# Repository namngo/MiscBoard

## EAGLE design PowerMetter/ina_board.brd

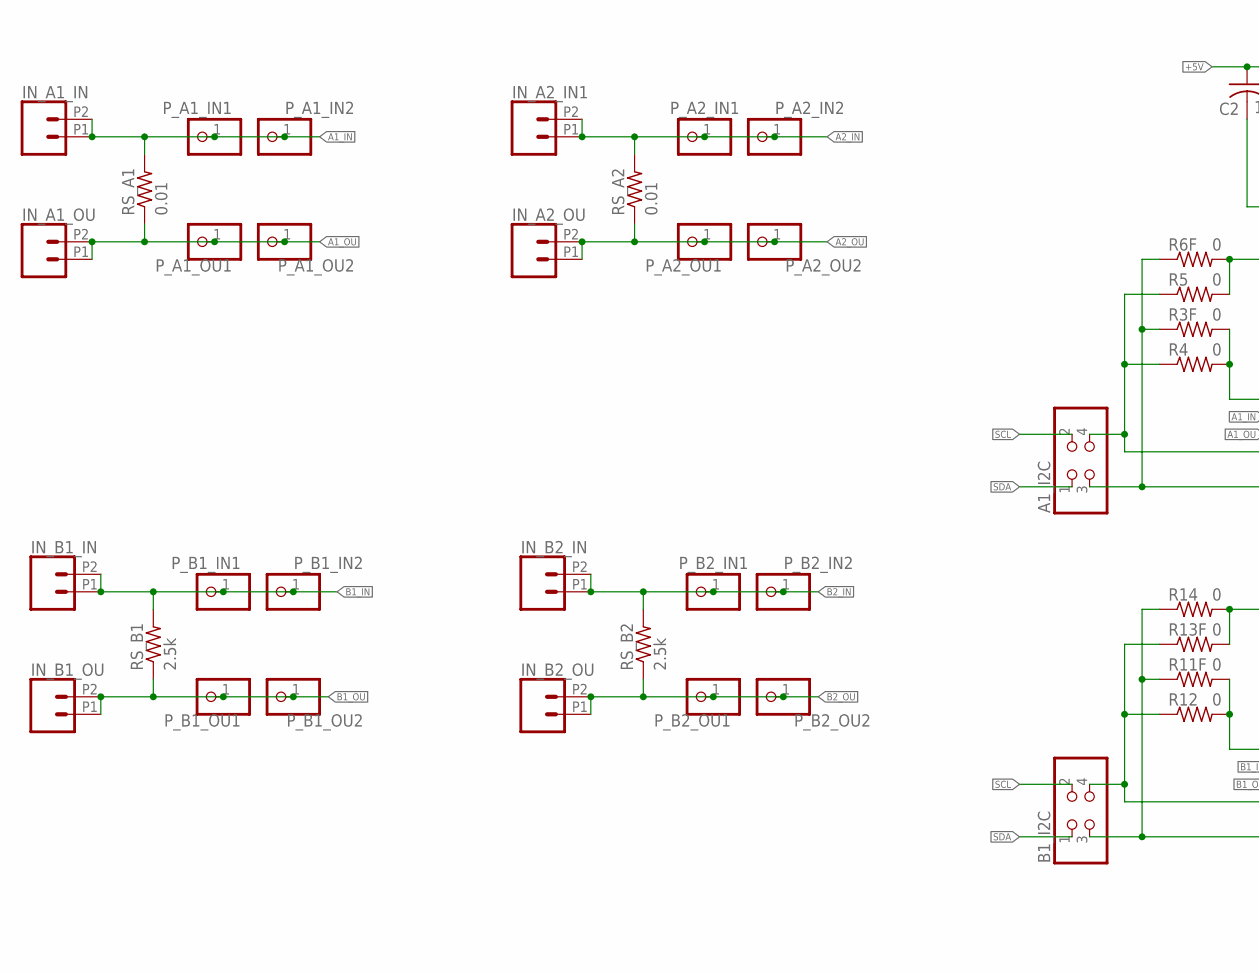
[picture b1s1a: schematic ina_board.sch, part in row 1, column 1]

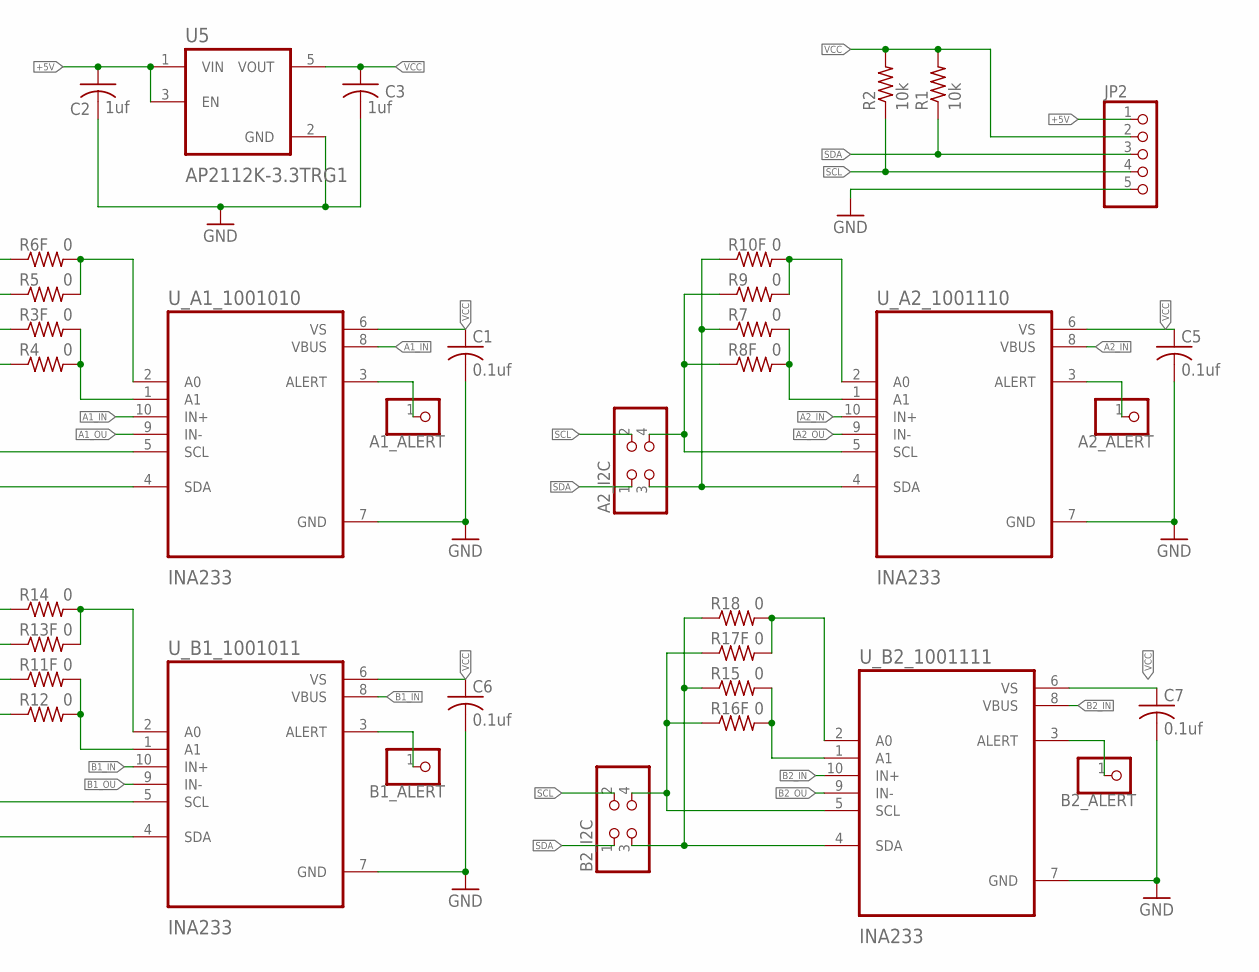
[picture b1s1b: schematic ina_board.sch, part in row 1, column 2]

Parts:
A1_ALERT, A2_ALERT: PINHD-1X1; 1X01
A1_I2C, A2_I2C: PINHD-2X2; 2X02
B1_ALERT, B2_ALERT: PINHD-1X1; 1X01
B1_I2C, B2_I2C: PINHD-2X2; 2X02
C1, C5, C6, C7: 0.1uf; C0805
C2, C3: 1uf; C1210
IN_A1_IN, IN_A1_OU, IN_A2_IN1, IN_A2_OU: CONN_022.54MM_SCREWTERM; 1X02_2.54_SCREWTERM
IN_B1_IN, IN_B1_OU, IN_B2_IN, IN_B2_OU: CONN_022.54MM_SCREWTERM; 1X02_2.54_SCREWTERM
JP2: PINHD-1X5; 1X05
P_A1_IN1, P_A1_IN2, P_A1_OU1, P_A1_OU2, P_A2_IN1, P_A2_IN2, P_A2_OU1, P_A2_OU2: PINHD-1X1; 1X01
P_B1_IN1, P_B1_IN2, P_B1_OU1, P_B1_OU2, P_B2_IN1, P_B2_IN2, P_B2_OU1, P_B2_OU2: PINHD-1X1; 1X01
R1, R2: 10k; R0805
R3F, R4, R5, R6F, R7, R8F, R9, R10F, R11F, R12, R13F, R14, R15, R16F, R17F, R18: 0; R0805
RS_A1, RS_A2: 0.01; R2512
RS_B1, RS_B2: 2.5k; R0805
U5: AP2112K-3.3TRG1; SOT95P285X140-5N
U_A1_1001010, U_A2_1001110: INA233; SOP50P490X110-10N
U_B1_1001011, U_B2_1001111: INA233; SOP50P490X110-10N

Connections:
+5V: C2.1, JP2.1, U5.1 (VIN), U5.3 (EN)
A1_IN: IN_A1_IN.P1 (1), IN_A1_IN.P2 (2), P_A1_IN1.1, P_A1_IN2.1, RS_A1.2, U_A1_1001010.8 (VBUS), U_A1_1001010.10 (IN+)
A1_OU: IN_A1_OU.P1 (1), IN_A1_OU.P2 (2), P_A1_OU1.1, P_A1_OU2.1, RS_A1.1, U_A1_1001010.9 (IN-)
A2_IN: IN_A2_IN1.P1 (1), IN_A2_IN1.P2 (2), P_A2_IN1.1, P_A2_IN2.1, RS_A2.2, U_A2_1001110.8 (VBUS), U_A2_1001110.10 (IN+)
A2_OU: IN_A2_OU.P1 (1), IN_A2_OU.P2 (2), P_A2_OU1.1, P_A2_OU2.1, RS_A2.1, U_A2_1001110.9 (IN-)
B1_IN: IN_B1_IN.P1 (1), IN_B1_IN.P2 (2), P_B1_IN1.1, P_B1_IN2.1, RS_B1.2, U_B1_1001011.8 (VBUS), U_B1_1001011.10 (IN+)
B1_OU: IN_B1_OU.P1 (1), IN_B1_OU.P2 (2), P_B1_OU1.1, P_B1_OU2.1, RS_B1.1, U_B1_1001011.9 (IN-)
B2_IN: IN_B2_IN.P1 (1), IN_B2_IN.P2 (2), P_B2_IN1.1, P_B2_IN2.1, RS_B2.2, U_B2_1001111.8 (VBUS), U_B2_1001111.10 (IN+)
B2_OU: IN_B2_OU.P1 (1), IN_B2_OU.P2 (2), P_B2_OU1.1, P_B2_OU2.1, RS_B2.1, U_B2_1001111.9 (IN-)
GND: C1.2, C2.2, C3.2, C5.2, C6.2, C7.2, JP2.5, U5.2 (GND), U_A1_1001010.7 (GND), U_A2_1001110.7 (GND), U_B1_1001011.7 (GND), U_B2_1001111.7 (GND)
unnamed: A2_I2C.4, R8F.1, R9.1, U_A2_1001110.5 (SCL)
unnamed: A2_I2C.3, R7.1, R10F.1, U_A2_1001110.4 (SDA)
unnamed: A1_ALERT.1, U_A1_1001010.3 (ALERT)
unnamed: R7.2, R8F.2, U_A2_1001110.1 (A1)
unnamed: A1_I2C.4, R4.1, R5.1, U_A1_1001010.5 (SCL)
unnamed: A1_I2C.3, R3F.1, R6F.1, U_A1_1001010.4 (SDA)
unnamed: R3F.2, R4.2, U_A1_1001010.1 (A1)
unnamed: R5.2, R6F.2, U_A1_1001010.2 (A0)
unnamed: R9.2, R10F.2, U_A2_1001110.2 (A0)
unnamed: A2_ALERT.1, U_A2_1001110.3 (ALERT)
unnamed: B1_I2C.4, R12.1, R13F.1, U_B1_1001011.5 (SCL)
unnamed: B1_I2C.3, R11F.1, R14.1, U_B1_1001011.4 (SDA)
unnamed: R11F.2, R12.2, U_B1_1001011.1 (A1)
unnamed: R13F.2, R14.2, U_B1_1001011.2 (A0)
unnamed: B1_ALERT.1, U_B1_1001011.3 (ALERT)
unnamed: B2_I2C.4, R16F.1, R17F.1, U_B2_1001111.5 (SCL)
unnamed: B2_I2C.3, R15.1, R18.1, U_B2_1001111.4 (SDA)
unnamed: R15.2, R16F.2, U_B2_1001111.1 (A1)
unnamed: R17F.2, R18.2, U_B2_1001111.2 (A0)
unnamed: B2_ALERT.1, U_B2_1001111.3 (ALERT)
SCL: A1_I2C.2, A2_I2C.2, B1_I2C.2, B2_I2C.2, JP2.4, R2.1
SDA: A1_I2C.1, A2_I2C.1, B1_I2C.1, B2_I2C.1, JP2.3, R1.1
VCC: C1.1, C3.1, C5.1, C6.1, C7.1, JP2.2, R1.2, R2.2, U5.5 (VOUT), U_A1_1001010.6 (VS), U_A2_1001110.6 (VS), U_B1_1001011.6 (VS), U_B2_1001111.6 (VS)

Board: 2 copper layers, 66 parts (29 on the bottom side), 33 nets, no tracks yet.

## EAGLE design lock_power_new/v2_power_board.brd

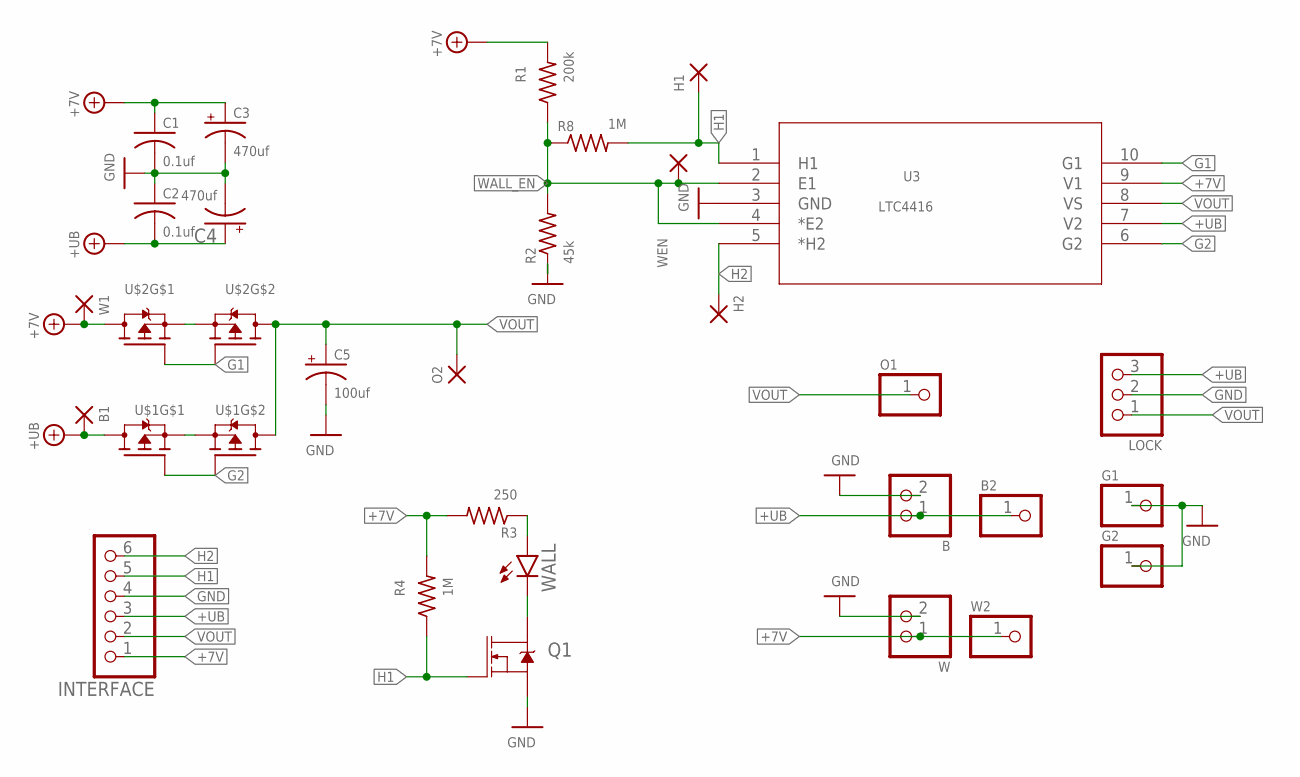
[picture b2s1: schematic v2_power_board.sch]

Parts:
B: PINHD-1X2; 1X02
B1: SMD2; SMD1,27-2,54
B2: PINHD-1X1; 1X01
C1, C2: 0.1uf; C0805
C3, C4: 470uf; 140CLH-0810
C5: 100uf; 140CLH-0810
G1, G2: PINHD-1X1; 1X01
H1, H2: SMD2; SMD1,27-2,54
INTERFACE: PINHD-1X6; 1X06
LOCK: PINHD-1X3; 1X03
O1: PINHD-1X1; 1X01
O2: SMD2; SMD1,27-2,54
Q1: 310mA/60V/1.6Ω; SOT323
R1: 200k; R0805
R2: 45k; R0805
R3: 250; R0805
R4, R8: 1M; R0805
U3: LTC4416; MSOP-10_MS
U$1, U$2: IRF7314PBF; SO-8
W: PINHD-1X2; 1X02
W1: SMD2; SMD1,27-2,54
W2: PINHD-1X1; 1X01
WALL: LEDSML0805; SML0805
WEN: SMD2; SMD1,27-2,54

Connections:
+7V: C1.1, C3.+, INTERFACE.1, R1.2, R3.2, R4.2, U3.9 (V1), U$2.7 (D), U$2.8 (D), W.1, W1.1, W2.1
+UB: B.1, B1.1, B2.1, C2.2, C4.+, INTERFACE.3, LOCK.3, U3.7 (V2), U$1.7 (D), U$1.8 (D)
G1: U3.10 (G1), U$2.2 (G), U$2.4 (G)
G2: U3.6 (G2), U$1.2 (G), U$1.4 (G)
GND: B.2, C1.2, C2.1, C3.-, C4.-, C5.-, G1.1, G2.1, INTERFACE.4, LOCK.2, Q1.2 (S), R2.1, U3.3 (GND), W.2
H1: H1.1, INTERFACE.5, Q1.1 (G), R4.1, R8.2, U3.1 (H1)
H2: H2.1, INTERFACE.6, U3.5 (*H2)
unnamed: R3.1, WALL.A
unnamed: Q1.3 (D), WALL.C
unnamed: U$1.1 (S), U$1.3 (S)
unnamed: U$2.1 (S), U$2.3 (S)
VOUT: C5.+, INTERFACE.2, LOCK.1, O1.1, O2.1, U3.8 (VS), U$1.5 (D), U$1.6 (D), U$2.5 (D), U$2.6 (D)
WALL_EN: R1.1, R2.2, R8.1, U3.2 (E1), U3.4 (*E2), WEN.1

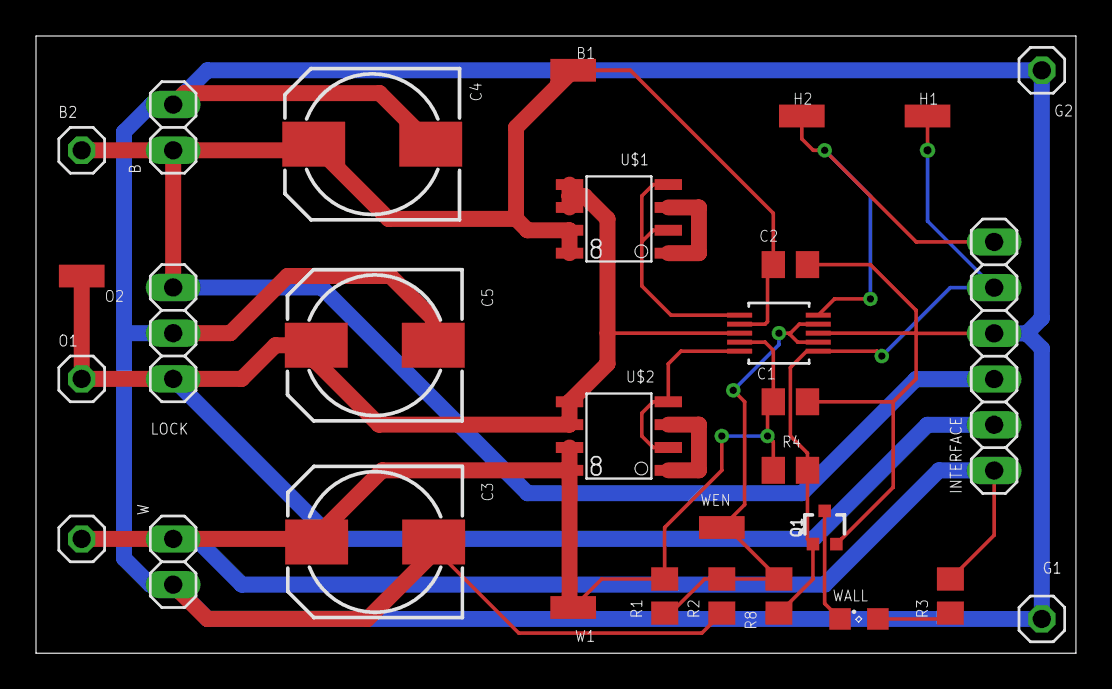
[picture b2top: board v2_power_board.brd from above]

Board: 2 copper layers, 57.8 x 34.3 mm, 30 parts (0 on the bottom side), 13 nets.

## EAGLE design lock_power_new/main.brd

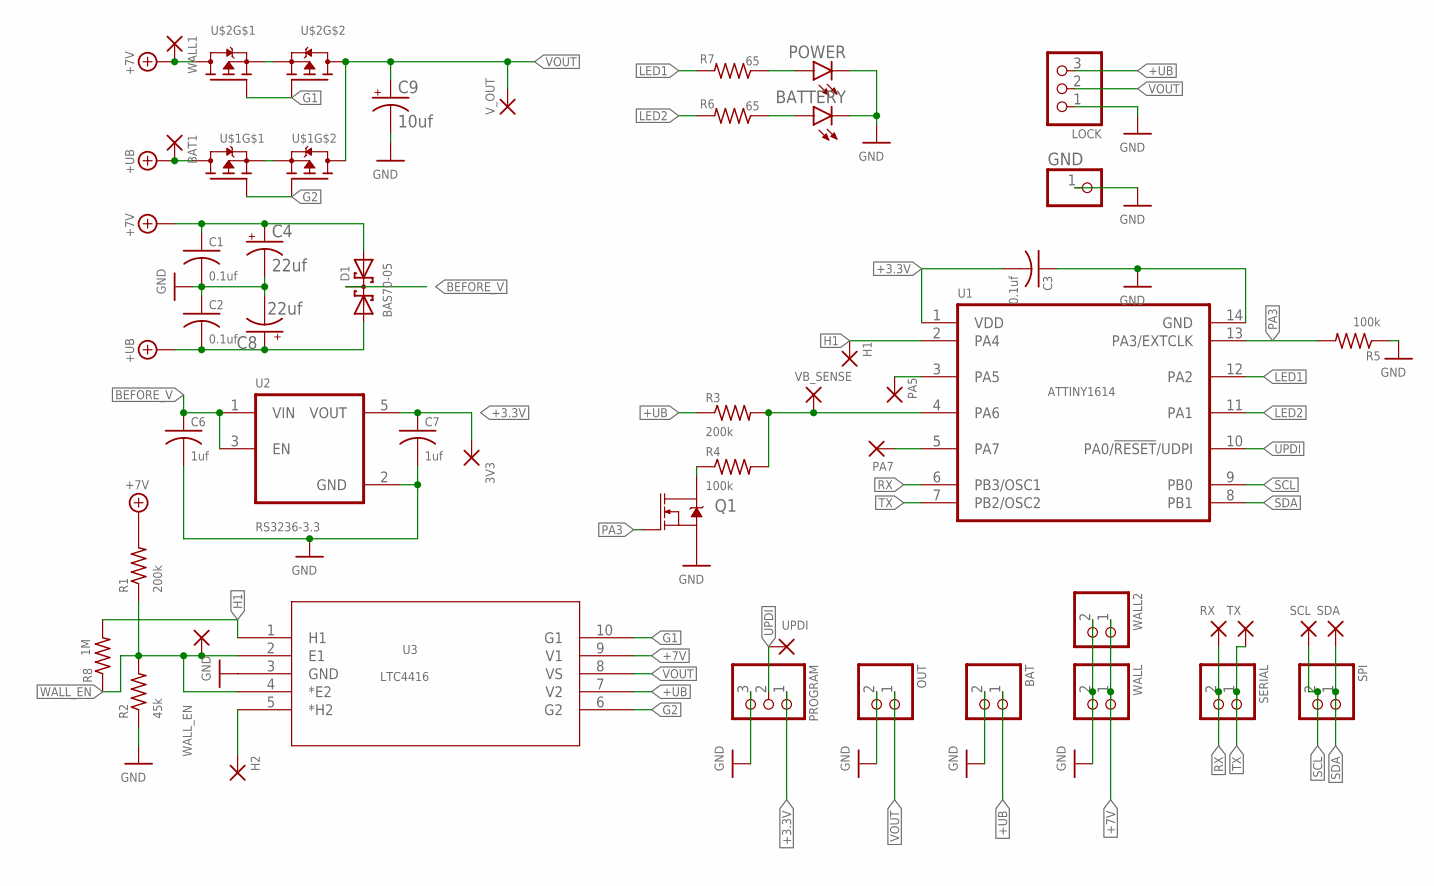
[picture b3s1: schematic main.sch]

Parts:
3V3: SMD2; SMD1,27-2,54
BAT: PINHD-1X2; 1X02
BAT1: SMD2; SMD1,27-2,54
BATTERY: LED5MM
C1, C2, C3: 0.1uf; C0805
C4, C8: 22uf; 153CLV-0405
C6, C7: 1uf; C1210
C9: 10uf; 153CLV-0405
D1: BAS70-05; SOT23
GND: PINHD-1X1; 1X01
H1, H2: SMD2; SMD1,27-2,54
LOCK: PINHD-1X3; 1X03
OUT: PINHD-1X2; 1X02
PA5, PA7: SMD2; SMD1,27-2,54
POWER: LED5MM
PROGRAM: PINHD-1X3; 1X03
Q1: 310mA/60V/1.6Ω; SOT323
R1, R3: 200k; R0805
R2: 45k; R0805
R4, R5: 100k; R0805
R6, R7: 65; R0805
R8: 1M; R0805
RX: SMD2; SMD1,27-2,54
SCL: SMD2; SMD1,27-2,54
SDA: SMD2; SMD1,27-2,54
SERIAL: PINHD-1X2; 1X02
SPI: PINHD-1X2; 1X02
TX: SMD2; SMD1,27-2,54
U1: ATTINY1614; SOIC127P600X175-14N
U2: RS3236-3.3; SOT95P285X140-5N
U3: LTC4416; MSOP-10_MS
U$1, U$2: IRF7314PBF; SO-8
UPDI: SMD2; SMD1,27-2,54
VB_SENSE: SMD2; SMD1,27-2,54
V_OUT: SMD2; SMD1,27-2,54
WALL, WALL2: PINHD-1X2; 1X02
WALL1: SMD2; SMD1,27-2,54
WALL_EN: SMD2; SMD1,27-2,54

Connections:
+3.3V: 3V3.1, C3.2, C7.1, PROGRAM.1, U1.1 (VDD), U2.5 (VOUT)
+7V: C1.1, C4.+, D1.2 (A2), R1.2, U3.9 (V1), U$2.7 (D), U$2.8 (D), WALL.1, WALL1.1, WALL2.1
+UB: BAT.1, BAT1.1, C2.2, C8.+, D1.1 (A1), LOCK.3, R3.1, U3.7 (V2), U$1.7 (D), U$1.8 (D)
BEFORE_V: C6.1, D1.3 (K1K2), U2.1 (VIN), U2.3 (EN)
G1: U3.10 (G1), U$2.2 (G), U$2.4 (G)
G2: U3.6 (G2), U$1.2 (G), U$1.4 (G)
GND: BAT.2, BATTERY.K (C), C1.2, C2.1, C3.1, C4.-, C6.2, C7.2, C8.-, C9.-, GND.1, LOCK.1, OUT.2, POWER.K (C), PROGRAM.3, Q1.2 (S), R2.1, R5.1, U1.14 (GND), U2.2 (GND), U3.3 (GND), WALL.2, WALL2.2
H1: H1.1, R8.2, U1.2 (PA4), U3.1 (H1)
LED1: R7.2, U1.12 (PA2)
LED2: R6.2, U1.11 (PA1)
unnamed: R3.2, R4.2, U1.4 (PA6), VB_SENSE.1
unnamed: PA7.1, U1.5 (PA7)
unnamed: U$1.1 (S), U$1.3 (S)
unnamed: U$2.1 (S), U$2.3 (S)
unnamed: POWER.A, R7.1
unnamed: H2.1, U3.5 (*H2)
unnamed: Q1.3 (D), R4.1
unnamed: PA5.1, U1.3 (PA5)
unnamed: BATTERY.A, R6.1
PA3: Q1.1 (G), R5.2, U1.13 (PA3/EXTCLK)
RX: RX.1, SERIAL.2, U1.6 (PB3/OSC1)
SCL: SCL.1, SPI.2, U1.9 (PB0)
SDA: SDA.1, SPI.1, U1.8 (PB1)
TX: SERIAL.1, TX.1, U1.7 (PB2/OSC2)
UPDI: PROGRAM.2, U1.10 (PA0/!RESET!/UDPI), UPDI.1
VOUT: C9.+, LOCK.2, OUT.1, U3.8 (VS), U$1.5 (D), U$1.6 (D), U$2.5 (D), U$2.6 (D), V_OUT.1
WALL_EN: R1.1, R2.2, R8.1, U3.2 (E1), U3.4 (*E2), WALL_EN.1

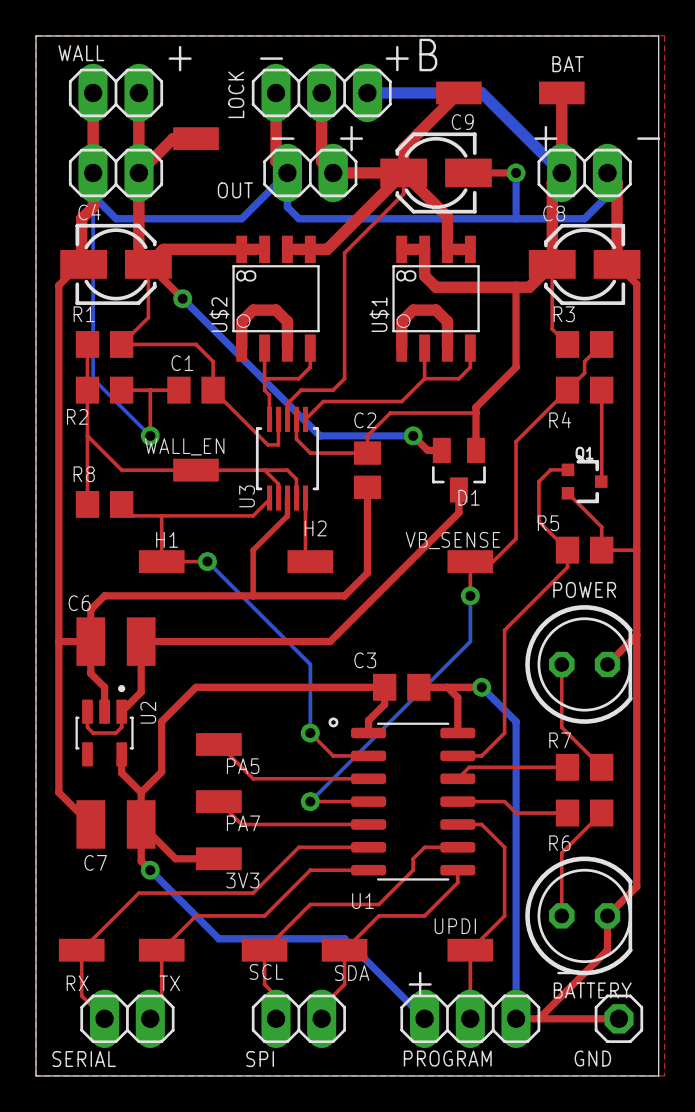
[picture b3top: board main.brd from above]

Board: 2 copper layers, 34.6 x 57.8 mm, 49 parts (0 on the bottom side), 27 nets.

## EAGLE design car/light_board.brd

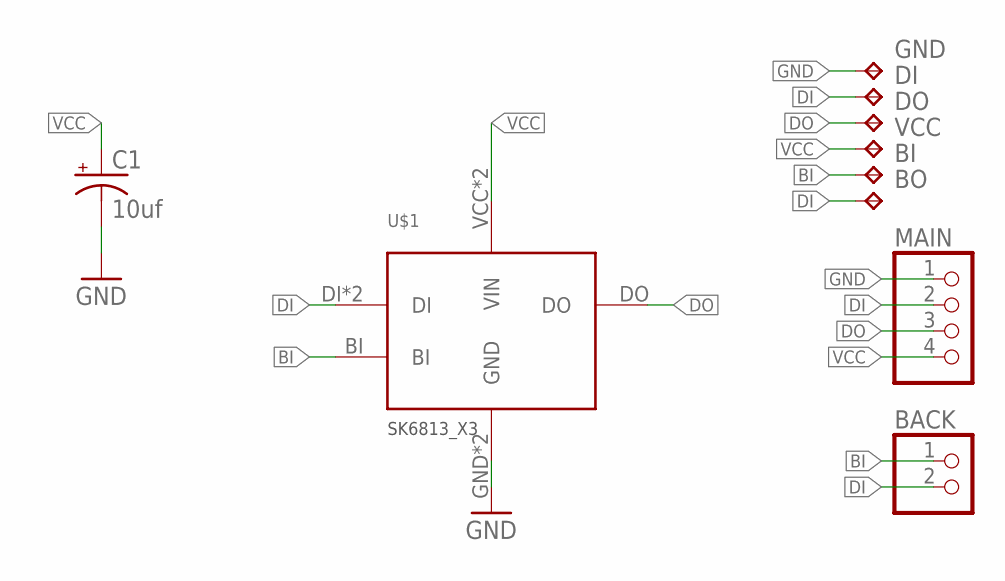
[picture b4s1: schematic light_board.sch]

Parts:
BACK: PINHD-1X2; 1X02
BI: TPB1,27; B1,27
BO: TPB1,27; B1,27
C1: 10uf; 153CLV-0405
DI: TPB1,27; B1,27
DO: TPB1,27; B1,27
GND: TPB1,27; B1,27
MAIN: PINHD-1X4; 1X04
U$1: SK6813_X3
VCC: TPB1,27; B1,27

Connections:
BI: BACK.1, BI.TP, U$1.BI
DI: BACK.2, BO.TP, DI.TP, MAIN.2, U$1.DI, U$1.DI@1 (DI)
DO: DO.TP, MAIN.3, U$1.DO
GND: C1.-, GND.TP, MAIN.1, U$1.GND, U$1.GND@1 (GND)
VCC: C1.+, MAIN.4, U$1.VCC (VIN), U$1.VCC@1 (VIN), VCC.TP

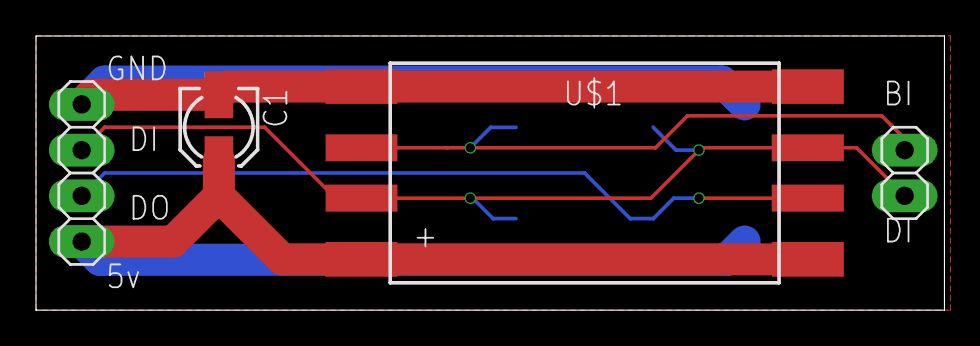
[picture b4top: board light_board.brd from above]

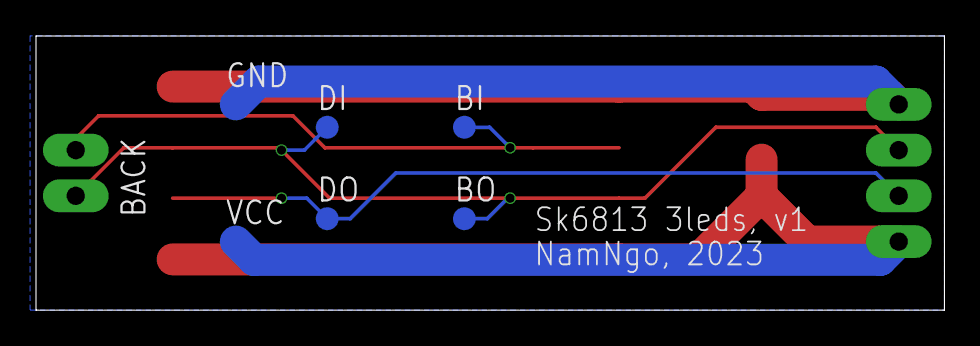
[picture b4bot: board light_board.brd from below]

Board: 2 copper layers, 50.5 x 15.2 mm, 10 parts (6 on the bottom side), 5 nets.

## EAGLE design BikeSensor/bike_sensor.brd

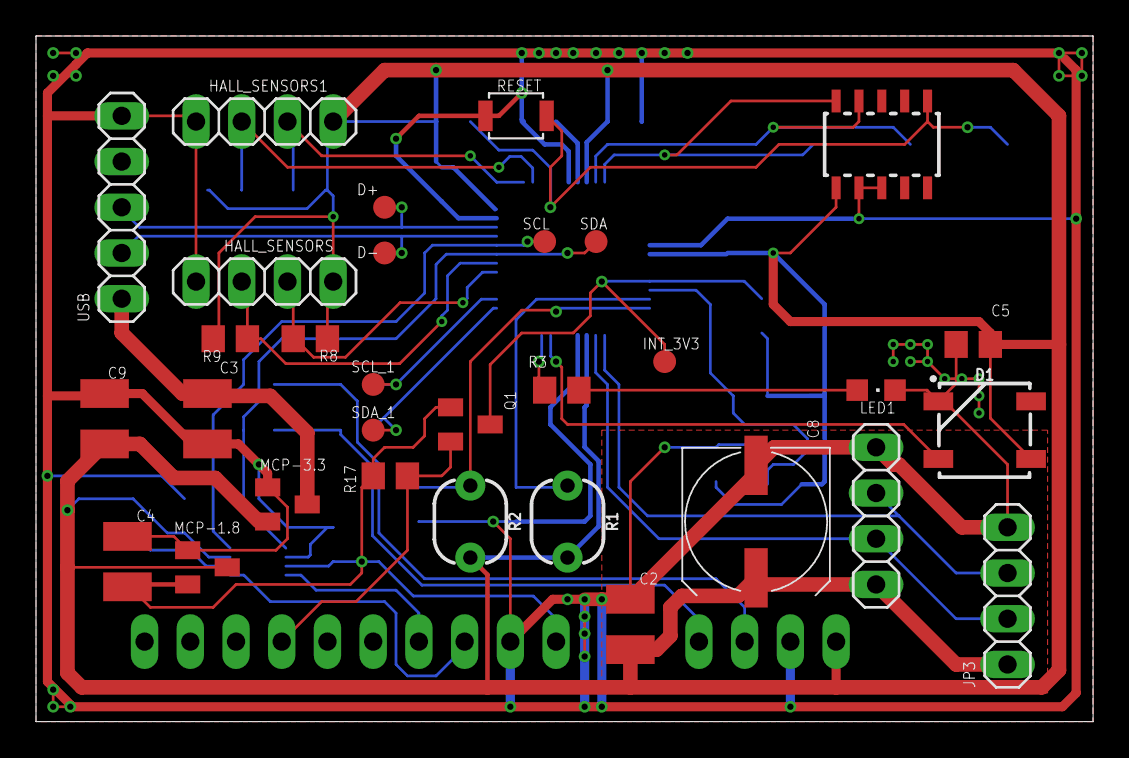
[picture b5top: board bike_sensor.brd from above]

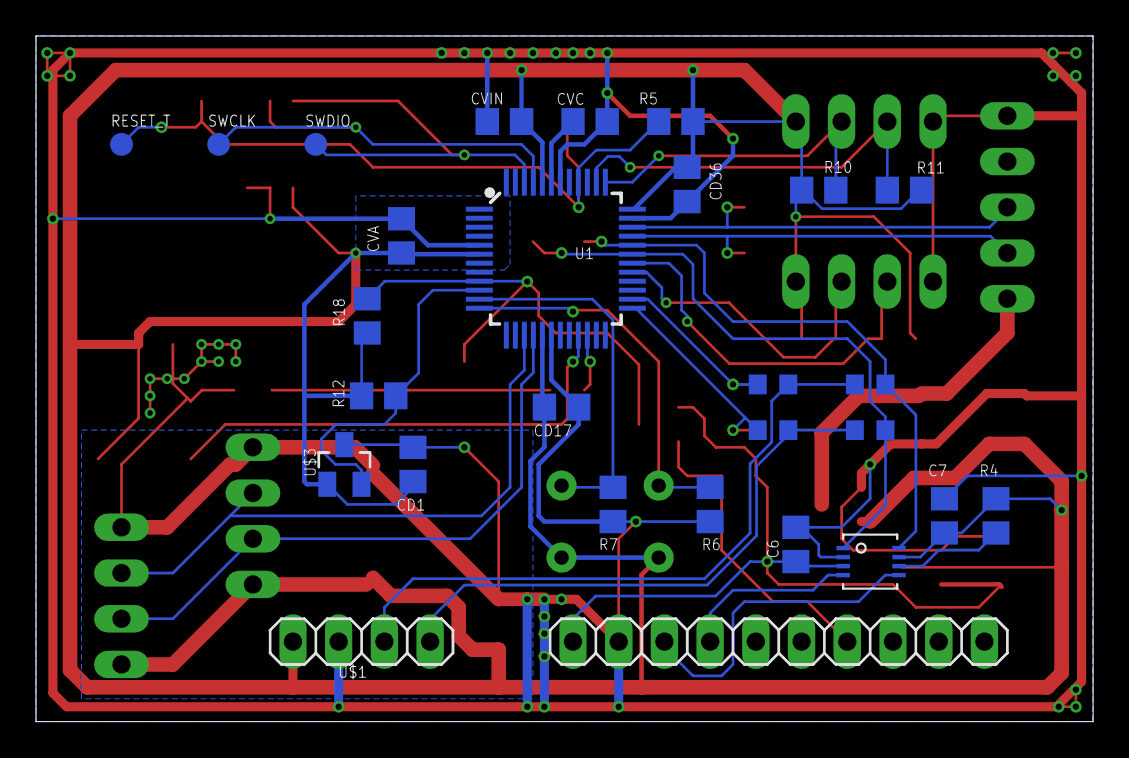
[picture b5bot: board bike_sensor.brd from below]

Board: 2 copper layers, 58.7 x 38.1 mm, 59 parts (28 on the bottom side), 33 nets.

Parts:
C2: 22uf; C1210
C3, C4, C9: 1uf; C1210
C5, C6, C7: 0.1uf; C0805
C8: 470uf; UD-8X10_NICHICON
CD1, CD17, CD36: 0.1uf; C0805
CVA: 0.1uf; C0805
CVC: 0.1uf; C0805
CVIN: 0.1uf; C0805
D1: WS2812B
D+: TPB1,27; B1,27
D-: TPB1,27; B1,27
HALL_SENSORS, HALL_SENSORS1: 1X04
INT_3V3: TPB1,27; B1,27
JP1: CORTEX_DEBUGSMD; SAMTECH_FTSH-105-01
JP2, JP3: 1X04
LED1: CHIPLED_0805
MCP-1.8, MCP-3.3: SOT23
Q1: BSS138; SOT23
R1, R2: PHOTOCELLPTH; PHOTOCELL
R3: 1.5k; R0805
R4, R5, R6, R8, R9, R10, R11, R12, R17, R18: 10k; R0805
R7: 1k; R0805
R13, R14, R15, R16: 0; R0603
RESET: B3U-1000P
RESET_T: TPB1,27; B1,27
SCL: TPB1,27; B1,27
SCL_1: TPB1,27; B1,27
SDA: TPB1,27; B1,27
SDA_1: TPB1,27; B1,27
SWCLK: TPB1,27; B1,27
SWDIO: TPB1,27; B1,27
U1: ATSAMD21G-A; TQFP-48
U$1: BMP280; BME280-BOARD
U$2: ICM-20948; ICM-20948-BOARD
U$3: AH1815; SOT23
U$5: TCA9406; DCU
USB: 1X05

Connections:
+1.8V: C4.1, C6.2, MCP-1.8.2, Q1.1, R17.1, U$2.10, U$5.P3
+3V3: C2.1, C5.2, C7.1, C8.+, C9.1, CD1.1, CD17.1, CD36.1, CVA.1, CVIN.1, D1.1, HALL_SENSORS.1, HALL_SENSORS1.1, JP1.1, JP2.1, JP3.1, MCP-1.8.3, MCP-3.3.2, R1.2, R2.2, R4.2, R5.1, R8.1, R9.1, R10.1, R11.1, R12.1, R18.1, U1.6, U1.17, U1.36, U1.44, U$1.1, U$3.1, U$5.P7
+5V: C3.1, MCP-3.3.3, USB.1
GND: C2.2, C3.2, C4.2, C5.1, C6.1, C7.2, C8.-, C9.2, CD1.2, CD17.2, CD36.2, CVA.2, CVC.2, CVIN.2, D1.3, HALL_SENSORS.4, HALL_SENSORS1.4, JP1.3, JP1.5, JP2.4, JP3.4, LED1.C, MCP-1.8.1, MCP-3.3.1, R6.2, R7.2, RESET.1, U1.5, U1.18, U1.35, U1.42, U$1.2, U$2.9, U$3.3, U$5.P2, USB.5
HALL_1: HALL_SENSORS.2, R8.2, U1.29
HALL_2: HALL_SENSORS.3, R9.2, U1.30
HALL_3: HALL_SENSORS1.2, R10.2, U1.37
HALL_4: HALL_SENSORS1.3, R11.2, U1.38
HALL_BOARD: R12.2, U1.10, U$3.2
INT_1V8: Q1.2, R17.2, U$2.4
INT_3V3: INT_3V3.TP, Q1.3, R18.2, U1.9
unnamed: CVC.1, U1.43
unnamed: R3.1, U1.22
unnamed: LED1.A, R3.2
unnamed: R4.1, U$5.P6
PHOTO_DARK: R2.1, R6.1, U1.12
PHOTO_LIGHT: R1.1, R7.1, U1.11
RESET: JP1.10, R5.2, RESET.2, RESET_T.TP, U1.40
RGB: D1.4, U1.21
RX: JP2.2, JP3.2, U1.16
SCL: R16.1, SCL.TP, U1.32, U$5.P8
SCL_1: R15.1, SCL_1.TP, U1.26
SCL_1V8: U$2.8, U$5.P5
SCL_3V3: R15.2, R16.2, U$1.3
SDA: R14.1, SDA.TP, U1.31, U$5.P1
SDA_1: R13.1, SDA_1.TP, U1.25
SDA_1V8: U$2.7, U$5.P4
SDA_3V3: R13.2, R14.2, U$1.4
SWCLK: JP1.4, SWCLK.TP, U1.45
SWDIO: JP1.2, SWDIO.TP, U1.46
TX: JP2.3, JP3.3, U1.15
USB_D+: D+.TP, U1.34, USB.3
USB_D-: D-.TP, U1.33, USB.2

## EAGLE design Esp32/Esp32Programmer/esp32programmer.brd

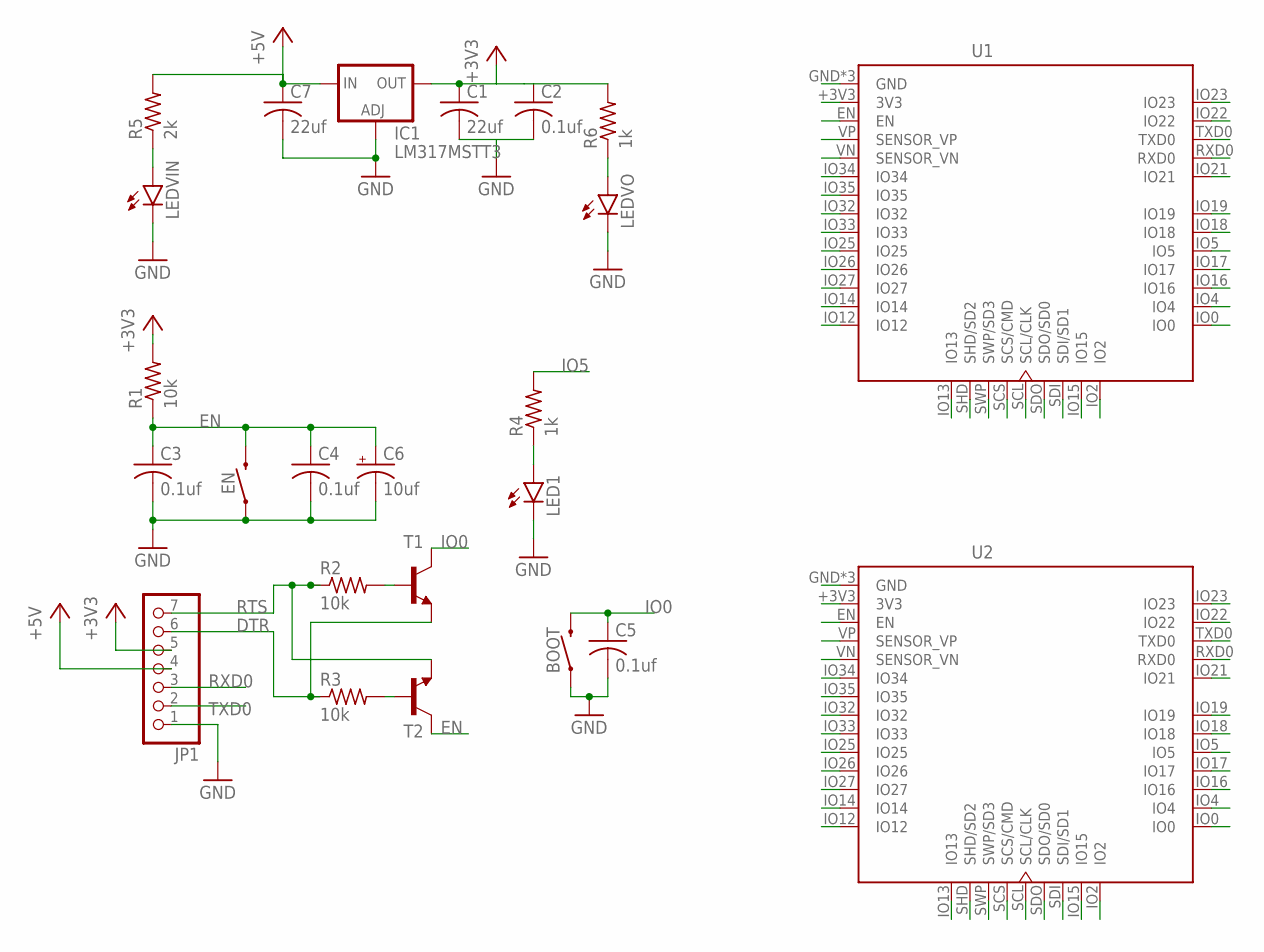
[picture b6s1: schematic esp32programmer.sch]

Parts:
BOOT: MOMENTARY-SWITCH-SPST-SMD-4.6X2.8MM; TACTILE_SWITCH_SMD_4.6X2.8MM
C1, C7: 22uf; C1210
C2, C3, C4, C5: 0.1uf; C0805
C6: 10uf; 153CLV-0605
EN: MOMENTARY-SWITCH-SPST-SMD-4.6X2.8MM; TACTILE_SWITCH_SMD_4.6X2.8MM
IC1: LM317MSTT3; SOT223
JP1: PINHD-1X7; 1X07
LED1: LEDSML0805; SML0805
LEDVIN: LEDSML0805; SML0805
LEDVO: LEDSML0805; SML0805
R1: 10k; R0805
R2, R3: 10k; M0805
R4, R6: 1k; R0805
R5: 2k; R0805
T1, T2: -NPN-SOT23-EBC; SOT23-EBC
U1, U2: ESP32-32DADAPTOR; ESP32_MODULE_ADAPTOR

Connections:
+3V3: C1.1, C2.1, IC1.4 (OUT), JP1.5, R1.2, R6.2, U1.+3V3 (3V3), U2.+3V3 (3V3)
+5V: C7.1, IC1.3 (IN), JP1.4, R5.2
DTR: JP1.6, R3.1, T1.E
EN: C3.1, C4.1, C6.+, EN.3 (2), EN.4 (2), R1.1, T2.C, U1.EN, U2.EN
GND: BOOT.1, BOOT.2 (1), C1.2, C2.2, C3.2, C4.2, C5.2, C6.-, C7.2, EN.1, EN.2 (1), IC1.1 (ADJ), JP1.1, LED1.C, LEDVIN.C, LEDVO.C, U1.GND, U1.GND@1 (GND), U1.GND@3 (GND), U2.GND, U2.GND@1 (GND), U2.GND@3 (GND)
IO0: BOOT.3 (2), BOOT.4 (2), C5.1, T1.C, U1.IO0, U2.IO0
IO2: U1.IO2, U2.IO2
IO4: U1.IO4, U2.IO4
IO5: R4.2, U1.IO5, U2.IO5
IO12: U1.IO12, U2.IO12
IO13: U1.IO13, U2.IO13
IO14: U1.IO14, U2.IO14
IO15: U1.IO15, U2.IO15
IO16: U1.IO16, U2.IO16
IO17: U1.IO17, U2.IO17
IO18: U1.IO18, U2.IO18
IO19: U1.IO19, U2.IO19
IO21: U1.IO21, U2.IO21
IO22: U1.IO22, U2.IO22
IO23: U1.IO23, U2.IO23
IO25: U1.IO25, U2.IO25
IO26: U1.IO26, U2.IO26
IO27: U1.IO27, U2.IO27
IO32: U1.IO32, U2.IO32
IO33: U1.IO33, U2.IO33
IO34: U1.IO34, U2.IO34
IO35: U1.IO35, U2.IO35
unnamed: R2.2, T1.B
unnamed: R3.2, T2.B
unnamed: LED1.A, R4.1
unnamed: LEDVIN.A, R5.1
unnamed: LEDVO.A, R6.1
RTS: JP1.7, R2.1, T2.E
RXD0: JP1.3, U1.RXD0, U2.RXD0
SCL: U1.SCL (SCL/CLK), U2.SCL (SCL/CLK)
SCS: U1.SCS (SCS/CMD), U2.SCS (SCS/CMD)
SDI: U1.SDI (SDI/SD1), U2.SDI (SDI/SD1)
SDO: U1.SDO (SDO/SD0), U2.SDO (SDO/SD0)
SHD: U1.SHD (SHD/SD2), U2.SHD (SHD/SD2)
SWP: U1.SWP (SWP/SD3), U2.SWP (SWP/SD3)
TXD0: JP1.2, U1.TXD0, U2.TXD0
VN: U1.VN (SENSOR_VN), U2.VN (SENSOR_VN)
VP: U1.VP (SENSOR_VP), U2.VP (SENSOR_VP)

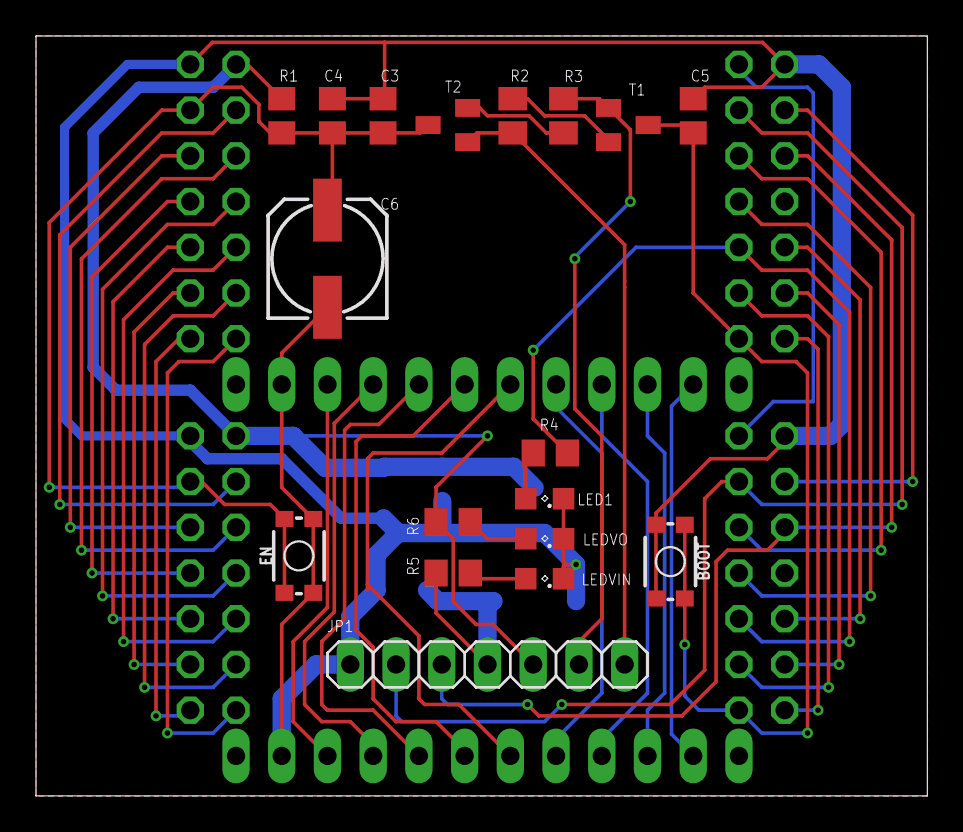
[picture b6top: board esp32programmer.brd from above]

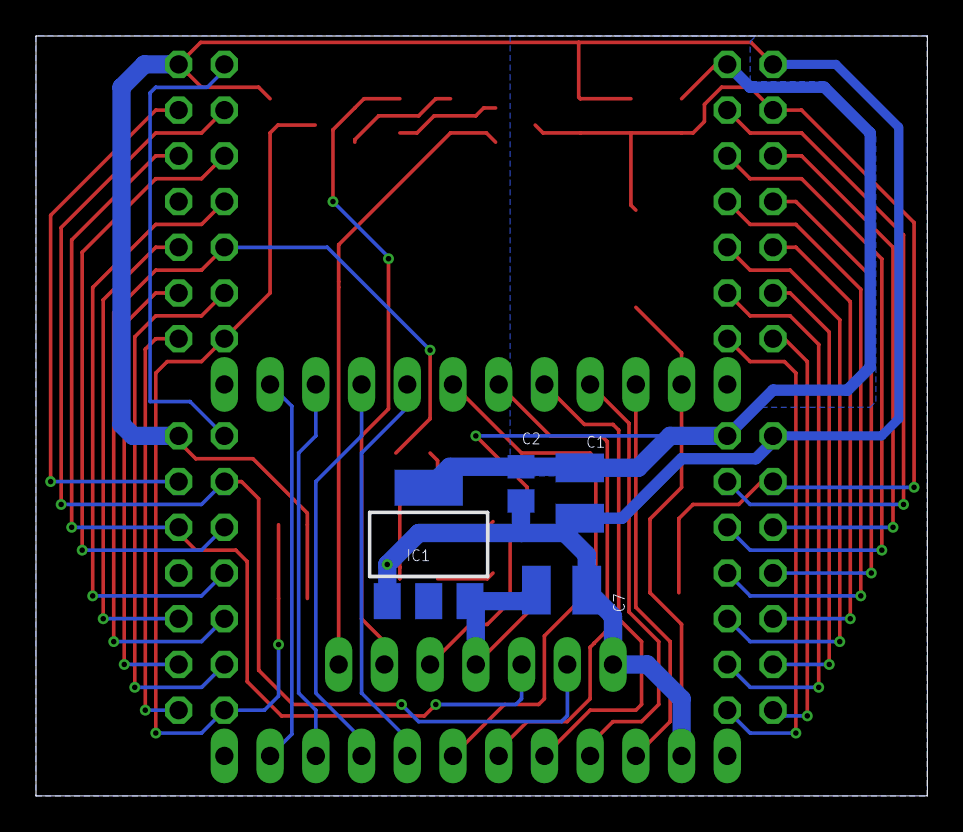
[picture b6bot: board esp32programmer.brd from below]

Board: 2 copper layers, 49.5 x 42.2 mm, 24 parts (4 on the bottom side), 43 nets.

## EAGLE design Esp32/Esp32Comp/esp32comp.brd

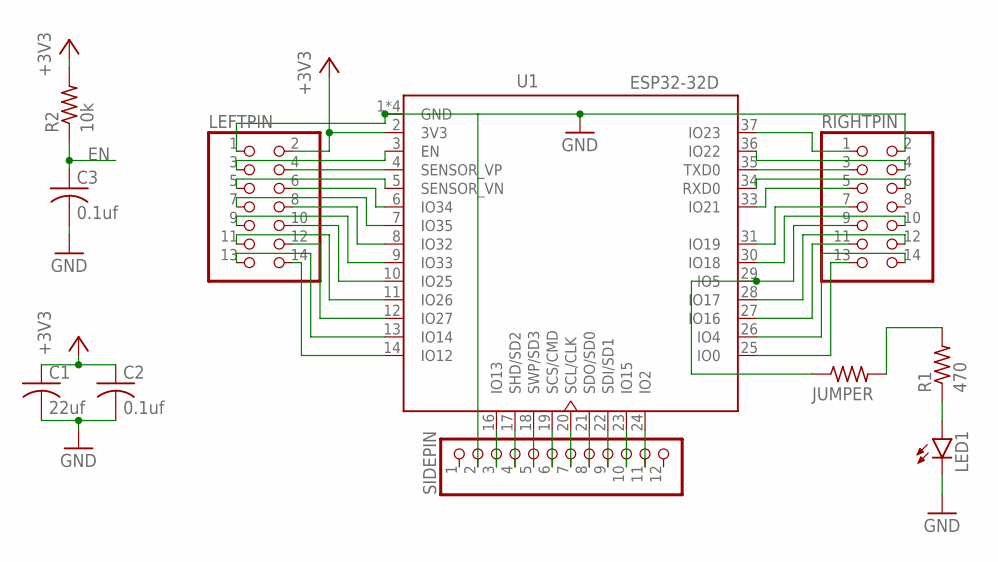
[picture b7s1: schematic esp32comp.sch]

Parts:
C1: 22uf; C1210
C2, C3: 0.1uf; C0805
JUMPER: RC0603JR-070RL; RES_0603
LED1: LEDSML0805; SML0805
LEFTPIN: PINHD-2X7; 2X07
R1: 470; R0805
R2: 10k; R0805
RIGHTPIN: PINHD-2X7; 2X07
SIDEPIN: PINHD-1X12; 1X12
U1: ESP32-32D; MODULE_ESP32-WROOM-32D

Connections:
+3V3: C1.1, C2.1, LEFTPIN.2, R2.2, U1.2 (3V3)
EN: C3.1, LEFTPIN.3, R2.1, U1.3 (EN)
GND: C1.2, C2.2, C3.2, LED1.C, LEFTPIN.1, RIGHTPIN.2, SIDEPIN.2, U1.1 (GND), U1.15 (GND), U1.38 (GND), U1.39 (GND)
IO0: RIGHTPIN.13, U1.25 (IO0)
IO2: SIDEPIN.11, U1.24 (IO2)
unnamed: LED1.A, R1.1
unnamed: JUMPER.2, R1.2
unnamed: SIDEPIN.10, U1.23 (IO15)
unnamed: SIDEPIN.3, U1.16 (IO13)
unnamed: LEFTPIN.4, U1.4 (SENSOR_VP)
unnamed: LEFTPIN.5, U1.5 (SENSOR_VN)
unnamed: LEFTPIN.6, U1.6 (IO34)
unnamed: LEFTPIN.7, U1.7 (IO35)
unnamed: LEFTPIN.8, U1.8 (IO32)
unnamed: LEFTPIN.9, U1.9 (IO33)
unnamed: LEFTPIN.10, U1.10 (IO25)
unnamed: LEFTPIN.11, U1.11 (IO26)
unnamed: LEFTPIN.12, U1.12 (IO27)
unnamed: LEFTPIN.13, U1.13 (IO14)
unnamed: LEFTPIN.14, U1.14 (IO12)
unnamed: RIGHTPIN.1, U1.37 (IO23)
unnamed: RIGHTPIN.4, U1.36 (IO22)
unnamed: RIGHTPIN.5, U1.33 (IO21)
unnamed: RIGHTPIN.7, U1.31 (IO19)
unnamed: RIGHTPIN.10, U1.30 (IO18)
unnamed: JUMPER.1, RIGHTPIN.9, U1.29 (IO5)
unnamed: RIGHTPIN.12, U1.28 (IO17)
unnamed: RIGHTPIN.11, U1.27 (IO16)
unnamed: RIGHTPIN.14, U1.26 (IO4)
RXD0: RIGHTPIN.6, U1.34 (RXD0)
SCL/CLK: SIDEPIN.7, U1.20 (SCL/CLK)
SCS/CMD: SIDEPIN.6, U1.19 (SCS/CMD)
SDI/SD1: SIDEPIN.9, U1.22 (SDI/SD1)
SDO/SD0: SIDEPIN.8, U1.21 (SDO/SD0)
SHD/SD2: SIDEPIN.4, U1.17 (SHD/SD2)
SWP/SD3: SIDEPIN.5, U1.18 (SWP/SD3)
TXD0: RIGHTPIN.3, U1.35 (TXD0)

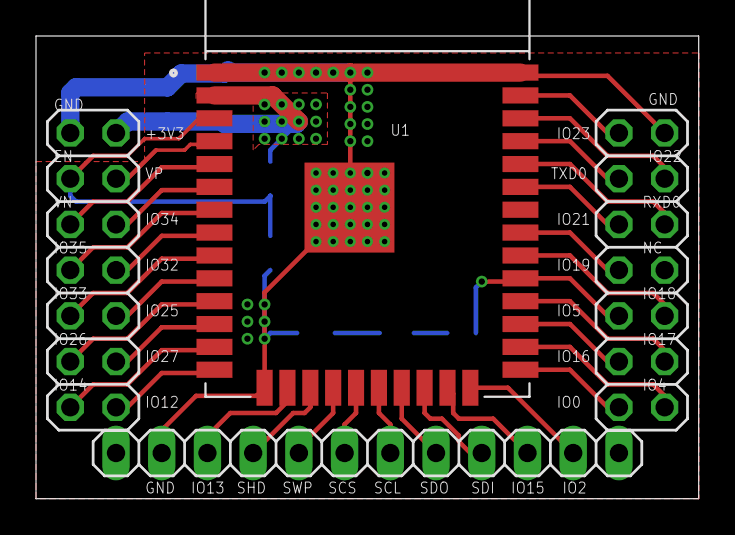
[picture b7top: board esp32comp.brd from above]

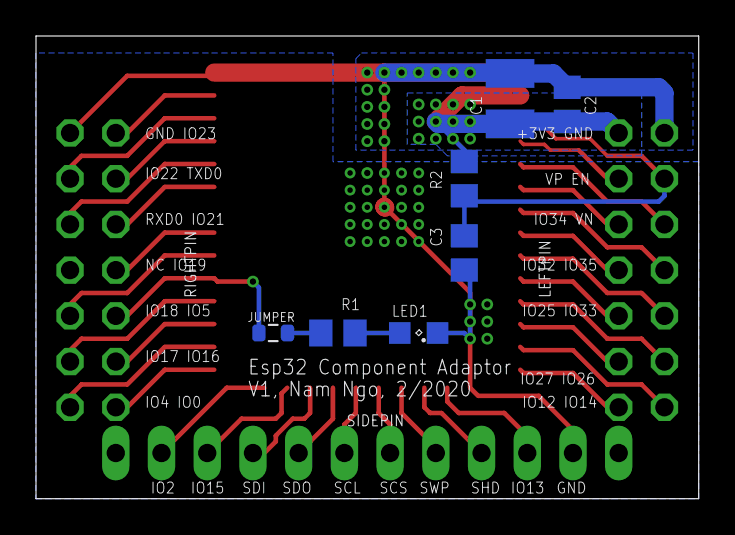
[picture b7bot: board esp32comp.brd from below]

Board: 2 copper layers, 36.8 x 25.7 mm, 11 parts (7 on the bottom side), 37 nets.

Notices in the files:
parts and their libraries:
SparkFun-Sensors: Licensing: Creative Commons ShareAlike 4.0 International - https://creativecommons.org/licenses/by-sa/4.0
inductor-bourns: Copyright (C) 2008, Bob Starr
